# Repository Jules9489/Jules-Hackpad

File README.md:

# Jules-Hackpad
My attempt at making a Macropad for Hack Club. It has 6 keys and 2 RGB LEDs. 

Overall Hackpad:

I couldn't find any models, so this is just the case, but imagine the parts are there

Schematic:

PCB:

BOM:

2x SK6812 MINI-E LEDs, 

4x M3x16mm screws, 

4x M3 Heatset, 

6x Blank DSA Keycaps, 

6x Cherry MX Switches, 

1x XIAO RP2040, 

1x 3D printed case, 

Challenges:
This was my first time doing anything so complicated. I had never even thought I could attempt something like this, but I am very happy with it.

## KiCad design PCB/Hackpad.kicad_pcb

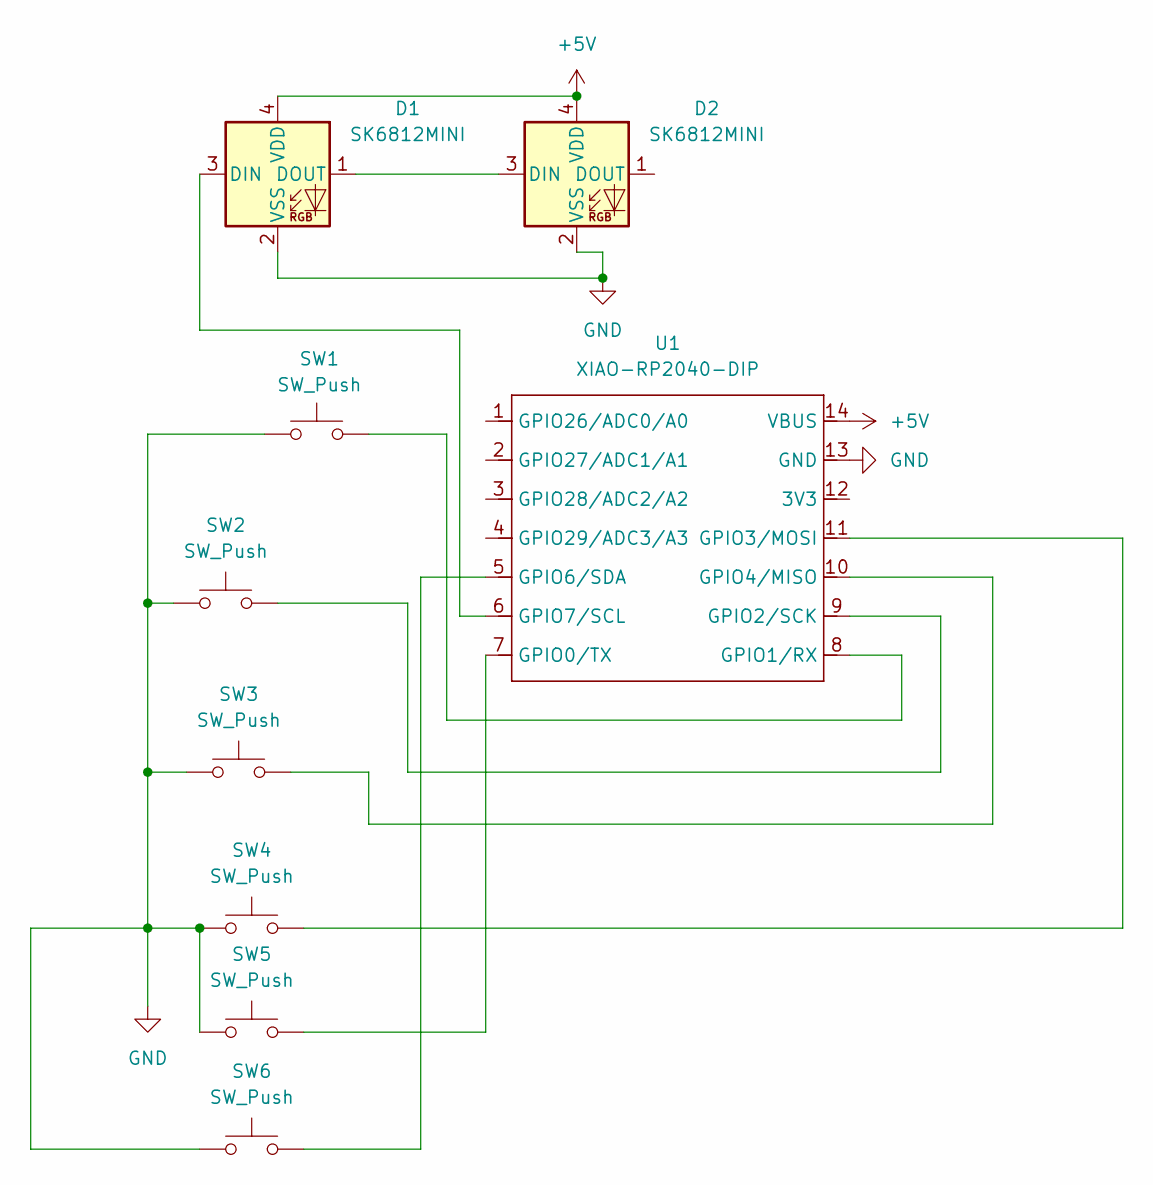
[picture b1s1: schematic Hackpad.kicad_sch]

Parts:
D1, D2: SK6812MINI; LED_SK6812MINI_PLCC4_3.5x3.5mm_P1.75mm
SW1, SW2, SW3, SW4, SW5, SW6: SW_Push; SW_Cherry_MX_1.00u_PCB
U1: XIAO-RP2040-DIP

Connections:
+5V: D1.4 (VDD), D2.4 (VDD), U1.14 (VBUS)
GND: D1.2 (VSS), D2.2 (VSS), SW1.1, SW2.1, SW3.1, SW4.1, SW5.1, SW6.1, U1.13 (GND)
unnamed: D1.3 (DIN), U1.6 (GPIO7/SCL)
unnamed: D1.1 (DOUT), D2.3 (DIN)
unnamed: SW5.2, U1.7 (GPIO0/TX)
unnamed: SW1.2, U1.8 (GPIO1/RX)
unnamed: SW2.2, U1.9 (GPIO2/SCK)
unnamed: SW4.2, U1.11 (GPIO3/MOSI)
unnamed: SW3.2, U1.10 (GPIO4/MISO)
unnamed: SW6.2, U1.5 (GPIO6/SDA)

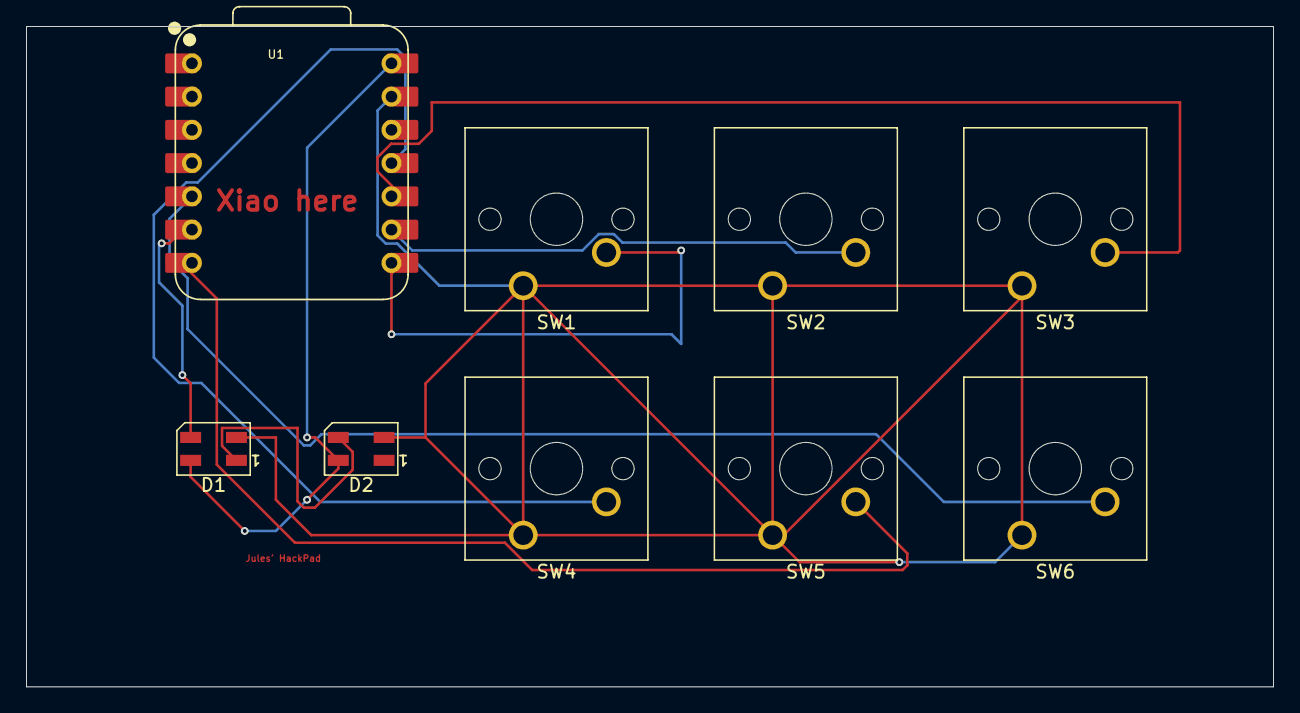
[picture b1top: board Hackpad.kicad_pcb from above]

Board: 2 copper layers, 95.3 x 50.4 mm, 9 parts (0 on the bottom side), 10 nets.

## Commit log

2025-12-02 Create Cad
2025-12-02 Add README
